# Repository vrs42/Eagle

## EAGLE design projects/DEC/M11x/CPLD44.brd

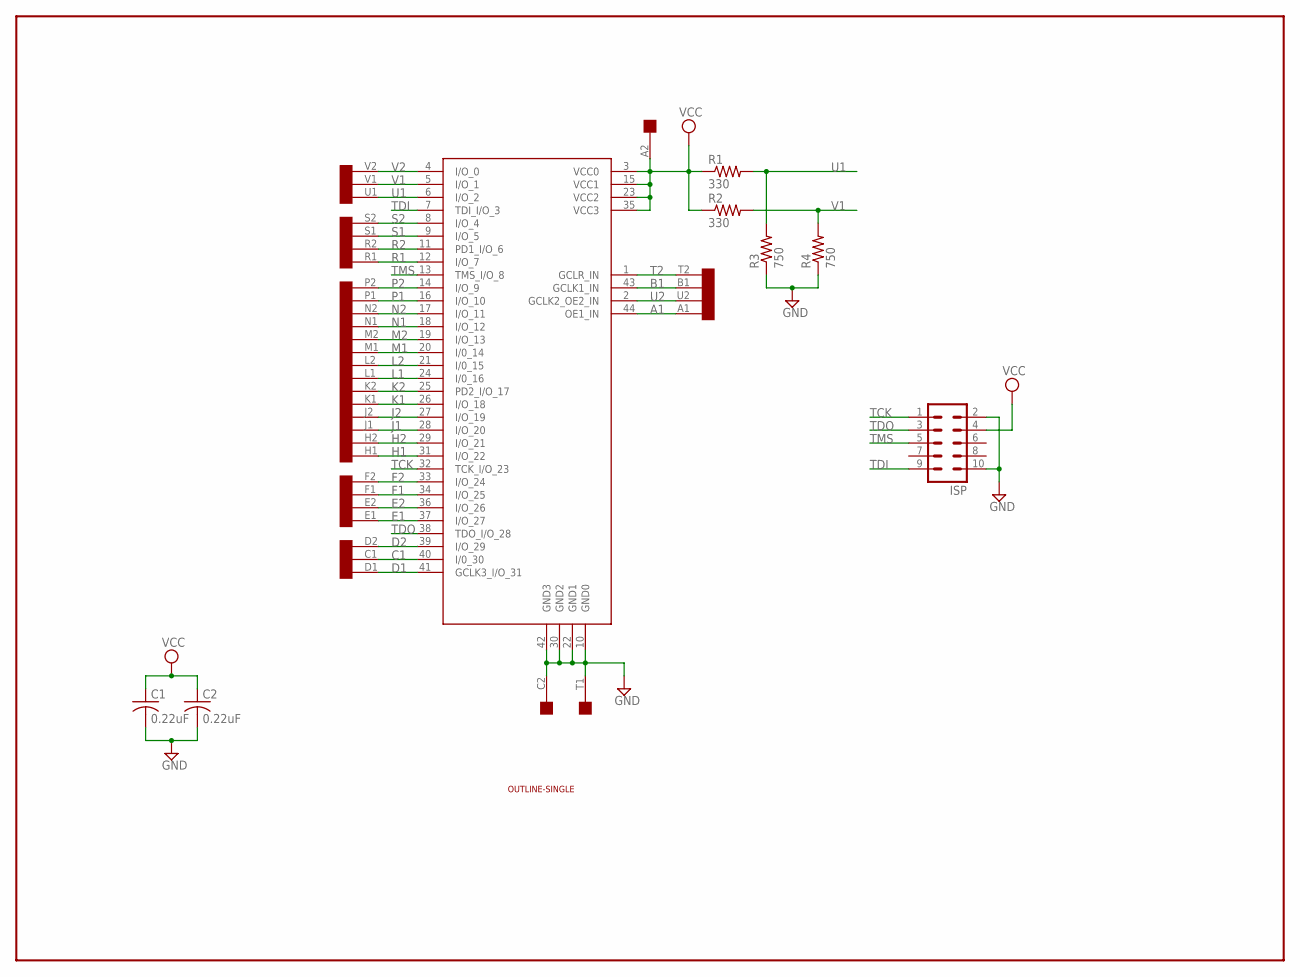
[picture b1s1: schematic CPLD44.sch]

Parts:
C1, C2: 0.22uF; C050-025X075
E1: ATF1502PLCC44; 3M44
ISP: MA05-2
R1, R2: 330; 0207/10
R3, R4: 750; 0207/10
U$1: SINGLE; EDGE-CON2
U$3: OUTLINE-SINGLE; SINGLE

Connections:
A1: E1.44 (OE1_IN), U$1.A1
B1: E1.43 (GCLK1_IN), U$1.B1
C1: E1.40 (I/0_30), U$1.C1
D1: E1.41 (GCLK3_I/O_31), U$1.D1
D2: E1.39 (I/O_29), U$1.D2
E1: E1.37 (I/O_27), U$1.E1
E2: E1.36 (I/O_26), U$1.E2
F1: E1.34 (I/O_25), U$1.F1
F2: E1.33 (I/O_24), U$1.F2
GND: C1.2, C2.2, E1.10 (GND0), E1.22 (GND1), E1.30 (GND2), E1.42 (GND3), ISP.2, ISP.10, R3.1, R4.1, U$1.C2, U$1.T1
H1: E1.31 (I/O_22), U$1.H1
H2: E1.29 (I/O_21), U$1.H2
J1: E1.28 (I/O_20), U$1.J1
J2: E1.27 (I/O_19), U$1.J2
K1: E1.26 (I/O_18), U$1.K1
K2: E1.25 (PD2_I/O_17), U$1.K2
L1: E1.24 (I/0_16), U$1.L1
L2: E1.21 (I/0_15), U$1.L2
M1: E1.20 (I/0_14), U$1.M1
M2: E1.19 (I/O_13), U$1.M2
N1: E1.18 (I/O_12), U$1.N1
N2: E1.17 (I/O_11), U$1.N2
P1: E1.16 (I/O_10), U$1.P1
P2: E1.14 (I/O_9), U$1.P2
R1: E1.12 (I/O_7), U$1.R1
R2: E1.11 (PD1_I/O_6), U$1.R2
S1: E1.9 (I/O_5), U$1.S1
S2: E1.8 (I/O_4), U$1.S2
T2: E1.1 (GCLR_IN), U$1.T2
TCK: E1.32 (TCK_I/O_23), ISP.1
TDI: E1.7 (TDI_I/O_3), ISP.9
TDO: E1.38 (TDO_I/O_28), ISP.3
TMS: E1.13 (TMS_I/O_8), ISP.5
U1: E1.6 (I/O_2), R1.2, R3.2, U$1.U1
U2: E1.2 (GCLK2_OE2_IN), U$1.U2
V1: E1.5 (I/O_1), R2.2, R4.2, U$1.V1
V2: E1.4 (I/O_0), U$1.V2
VCC: C1.1, C2.1, E1.3 (VCC0), E1.15 (VCC1), E1.23 (VCC2), E1.35 (VCC3), ISP.4, R1.1, R2.1, U$1.A2

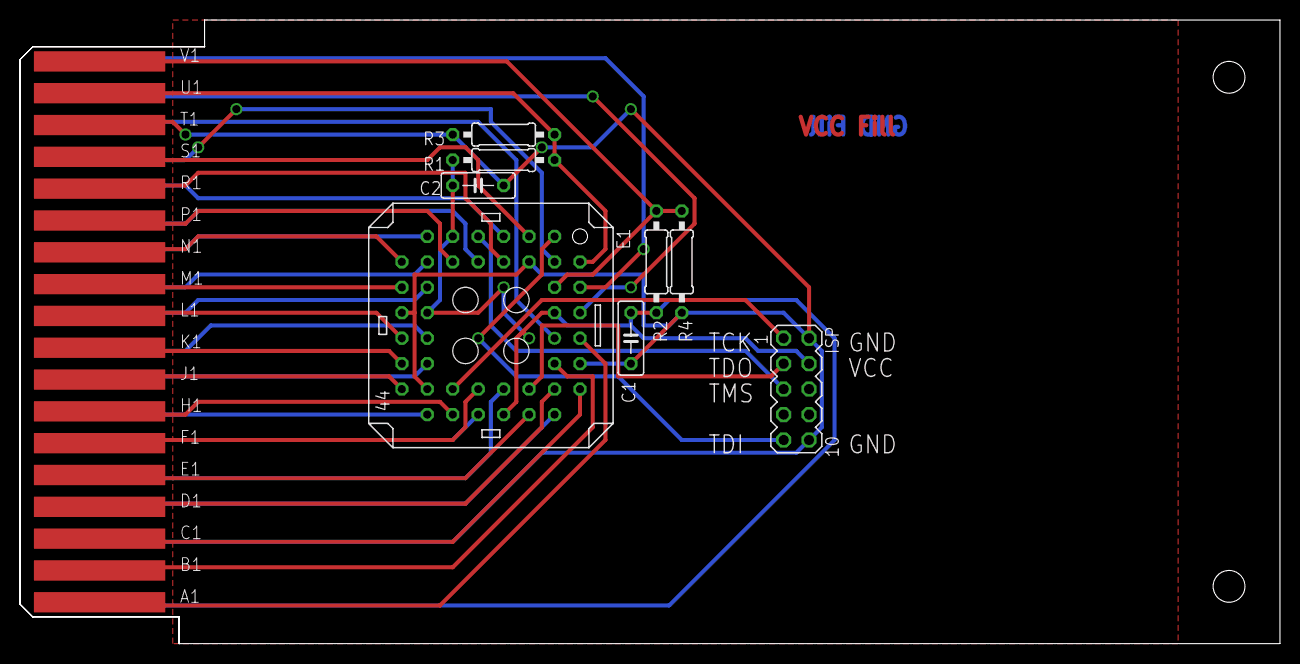
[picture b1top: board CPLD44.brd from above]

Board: 2 copper layers, 125.7 x 62.2 mm, 10 parts (0 on the bottom side), 38 nets.

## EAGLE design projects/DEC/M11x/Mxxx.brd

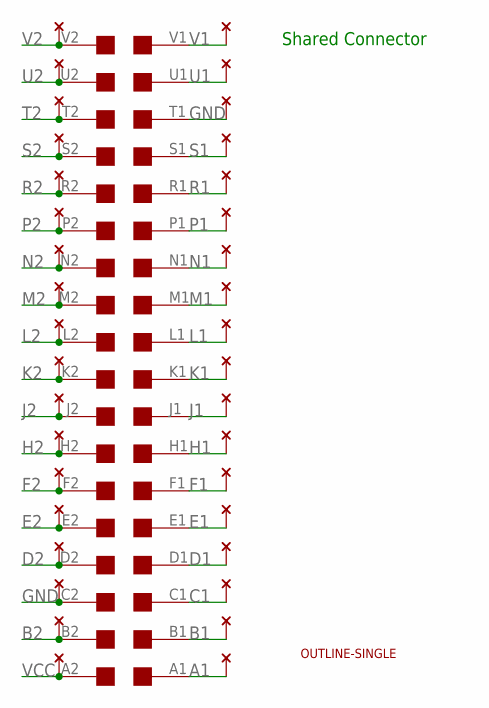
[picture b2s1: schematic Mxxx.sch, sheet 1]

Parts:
U$1: EDGE-2CONNECTOR; EDGE-CON2
U$4: THRU-HOLE2A; THRU-HOLEA
U$5: OUTLINE-SINGLE; SINGLE

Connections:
A1: U$1.A1, U$4.A1; also elsewhere on the board
B1: U$1.B1, U$4.B1; also elsewhere on the board
B2: U$1.B2, U$4.B2
C1: U$1.C1, U$4.C1; also elsewhere on the board
D1: U$1.D1, U$4.D1; also elsewhere on the board
D2: U$1.D2, U$4.D2; also elsewhere on the board
E1: U$1.E1, U$4.E1; also elsewhere on the board
E2: U$1.E2, U$4.E2; also elsewhere on the board
F1: U$1.F1, U$4.F1; also elsewhere on the board
F2: U$1.F2, U$4.F2; also elsewhere on the board
GND: U$1.C2, U$1.T1, U$4.C2, U$4.T1; also elsewhere on the board
H1: U$1.H1, U$4.H1; also elsewhere on the board
H2: U$1.H2, U$4.H2; also elsewhere on the board
J1: U$1.J1, U$4.J1; also elsewhere on the board
J2: U$1.J2, U$4.J2; also elsewhere on the board
K1: U$1.K1, U$4.K1; also elsewhere on the board
K2: U$1.K2, U$4.K2; also elsewhere on the board
L1: U$1.L1, U$4.L1; also elsewhere on the board
L2: U$1.L2, U$4.L2; also elsewhere on the board
M1: U$1.M1, U$4.M1; also elsewhere on the board
M2: U$1.M2, U$4.M2; also elsewhere on the board
N1: U$1.N1, U$4.N1; also elsewhere on the board
N2: U$1.N2, U$4.N2; also elsewhere on the board
P1: U$1.P1, U$4.P1; also elsewhere on the board
P2: U$1.P2, U$4.P2; also elsewhere on the board
R1: U$1.R1, U$4.R1; also elsewhere on the board
R2: U$1.R2, U$4.R2; also elsewhere on the board
S1: U$1.S1, U$4.S2; also elsewhere on the board
S2: U$1.S2, U$4.S1; also elsewhere on the board
T2: U$1.T2, U$4.T2; also elsewhere on the board
U1: U$1.U1, U$4.U1; also elsewhere on the board
U2: U$1.U2, U$4.U2; also elsewhere on the board
V1: U$1.V1, U$4.V1; also elsewhere on the board
V2: U$1.V2, U$4.V2; also elsewhere on the board
VCC: U$1.A2, U$4.A2; also elsewhere on the board

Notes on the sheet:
Shared Connector

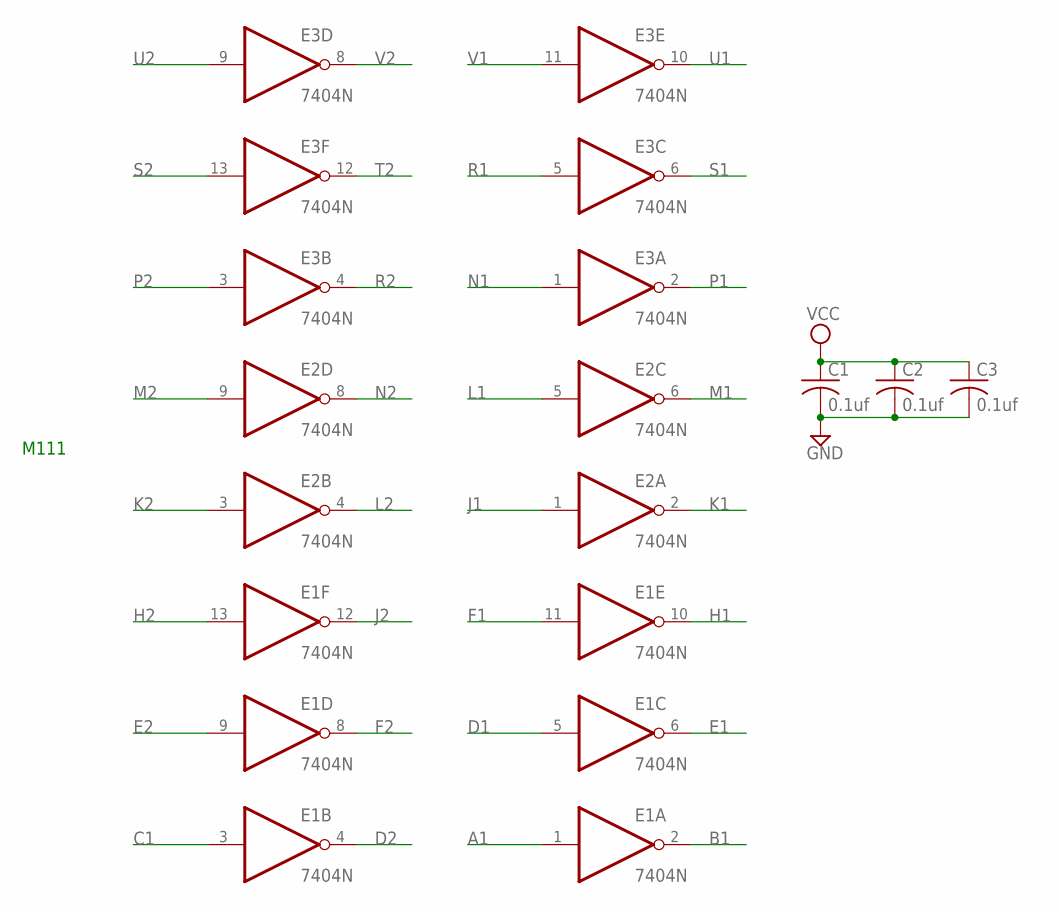
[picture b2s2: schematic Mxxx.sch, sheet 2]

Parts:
C1, C2, C3: 0.1uf; C050-025X075
E1, E2, E3: 7404N; DIL14

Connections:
A1: E1.1 (I); also elsewhere on the board
B1: E1.2 (O); also elsewhere on the board
C1: E1.3 (I); also elsewhere on the board
D1: E1.5 (I); also elsewhere on the board
D2: E1.4 (O); also elsewhere on the board
E1: E1.6 (O); also elsewhere on the board
E2: E1.9 (I); also elsewhere on the board
F1: E1.11 (I); also elsewhere on the board
F2: E1.8 (O); also elsewhere on the board
GND: C1.2, C2.2, C3.2, E1.7 (GND), E2.7 (GND), E3.7 (GND); also elsewhere on the board
H1: E1.10 (O); also elsewhere on the board
H2: E1.13 (I); also elsewhere on the board
J1: E2.1 (I); also elsewhere on the board
J2: E1.12 (O); also elsewhere on the board
K1: E2.2 (O); also elsewhere on the board
K2: E2.3 (I); also elsewhere on the board
L1: E2.5 (I); also elsewhere on the board
L2: E2.4 (O); also elsewhere on the board
M1: E2.6 (O); also elsewhere on the board
M2: E2.9 (I); also elsewhere on the board
N1: E3.1 (I); also elsewhere on the board
N2: E2.8 (O); also elsewhere on the board
P1: E3.2 (O); also elsewhere on the board
P2: E3.3 (I); also elsewhere on the board
R1: E3.5 (I); also elsewhere on the board
R2: E3.4 (O); also elsewhere on the board
S1: E3.6 (O); also elsewhere on the board
S2: E3.13 (I); also elsewhere on the board
T2: E3.12 (O); also elsewhere on the board
U1: E3.10 (O); also elsewhere on the board
U2: E3.9 (I); also elsewhere on the board
V1: E3.11 (I); also elsewhere on the board
V2: E3.8 (O); also elsewhere on the board
VCC: C1.1, C2.1, C3.1, E1.14 (VCC), E2.14 (VCC), E3.14 (VCC); also elsewhere on the board

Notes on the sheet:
M111

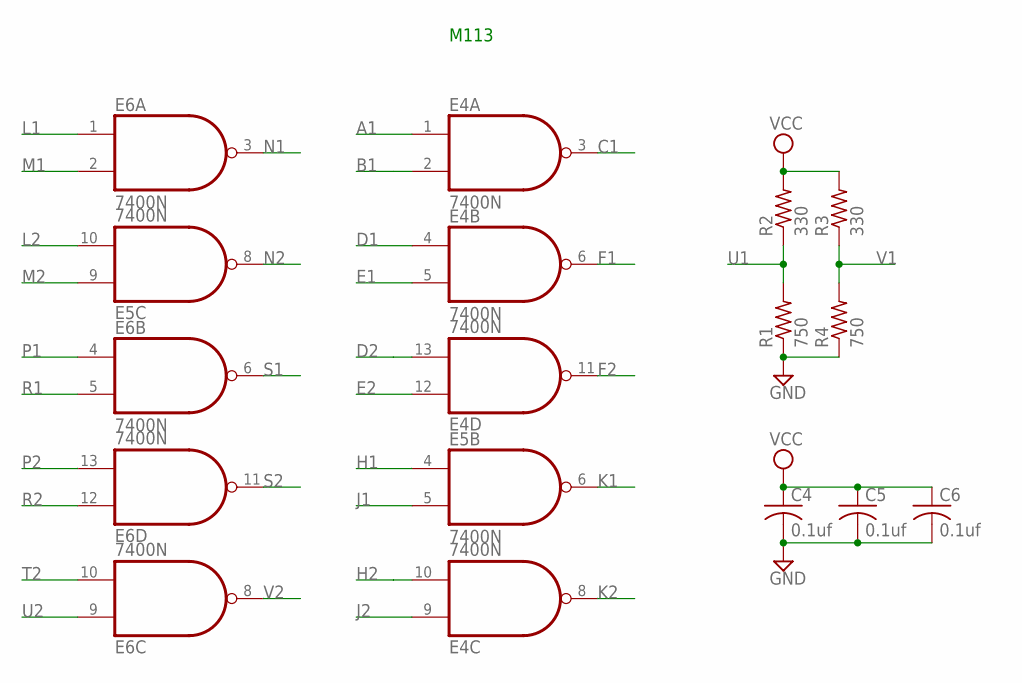
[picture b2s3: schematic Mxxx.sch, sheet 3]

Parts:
C4, C5, C6: 0.1uf; C050-025X075
E4, E5, E6: 7400N; DIL14
R1, R4: 750; 0207/10
R2, R3: 330; 0207/10

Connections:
A1: E4.1 (I0); also elsewhere on the board
B1: E4.2 (I1); also elsewhere on the board
C1: E4.3 (O); also elsewhere on the board
D1: E4.4 (I0); also elsewhere on the board
D2: E4.13 (I1); also elsewhere on the board
E1: E4.5 (I1); also elsewhere on the board
E2: E4.12 (I0); also elsewhere on the board
F1: E4.6 (O); also elsewhere on the board
F2: E4.11 (O); also elsewhere on the board
GND: C4.2, C5.2, C6.2, E4.7 (GND), E5.7 (GND), E6.7 (GND), R1.1, R4.1; also elsewhere on the board
H1: E5.4 (I0); also elsewhere on the board
H2: E4.10 (I1); also elsewhere on the board
J1: E5.5 (I1); also elsewhere on the board
J2: E4.9 (I0); also elsewhere on the board
K1: E5.6 (O); also elsewhere on the board
K2: E4.8 (O); also elsewhere on the board
L1: E6.1 (I0); also elsewhere on the board
L2: E5.10 (I1); also elsewhere on the board
M1: E6.2 (I1); also elsewhere on the board
M2: E5.9 (I0); also elsewhere on the board
N1: E6.3 (O); also elsewhere on the board
N2: E5.8 (O); also elsewhere on the board
P1: E6.4 (I0); also elsewhere on the board
P2: E6.13 (I1); also elsewhere on the board
R1: E6.5 (I1); also elsewhere on the board
R2: E6.12 (I0); also elsewhere on the board
S1: E6.6 (O); also elsewhere on the board
S2: E6.11 (O); also elsewhere on the board
T2: E6.10 (I1); also elsewhere on the board
U1: R1.2, R2.1; also elsewhere on the board
U2: E6.9 (I0); also elsewhere on the board
V1: R3.1, R4.2; also elsewhere on the board
V2: E6.8 (O); also elsewhere on the board
VCC: C4.1, C5.1, C6.1, E4.14 (VCC), E5.14 (VCC), E6.14 (VCC), R2.2, R3.2; also elsewhere on the board

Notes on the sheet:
M113

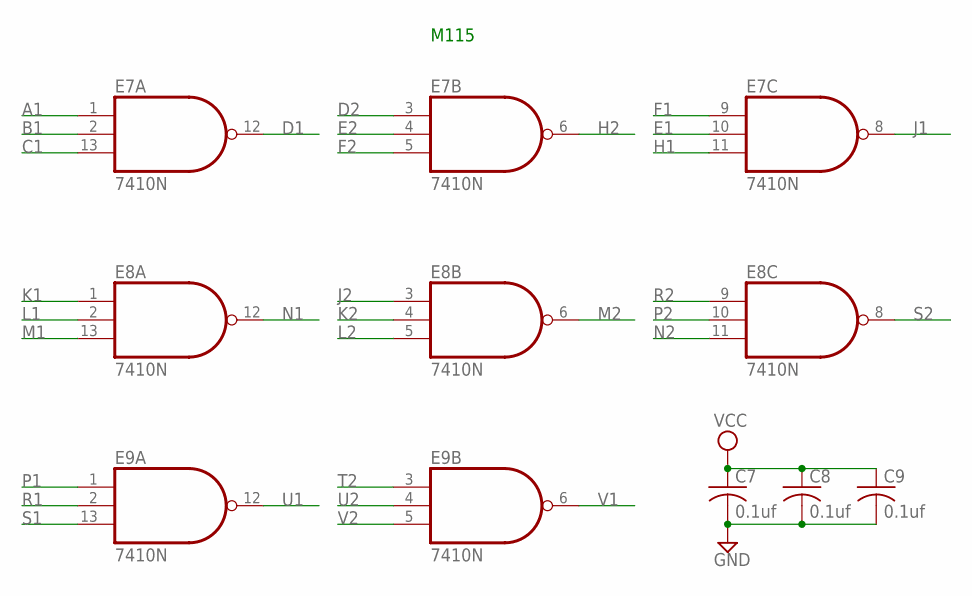
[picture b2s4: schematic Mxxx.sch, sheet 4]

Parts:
C7, C8, C9: 0.1uf; C050-025X075
E7, E8, E9: 7410N; DIL14

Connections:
A1: E7.1 (I0); also elsewhere on the board
B1: E7.2 (I1); also elsewhere on the board
C1: E7.13 (I2); also elsewhere on the board
D1: E7.12 (O); also elsewhere on the board
D2: E7.3 (I0); also elsewhere on the board
E1: E7.10 (I1); also elsewhere on the board
E2: E7.4 (I1); also elsewhere on the board
F1: E7.9 (I0); also elsewhere on the board
F2: E7.5 (I2); also elsewhere on the board
GND: C7.2, C8.2, C9.2, E7.7 (GND), E8.7 (GND), E9.7 (GND); also elsewhere on the board
H1: E7.11 (I2); also elsewhere on the board
H2: E7.6 (O); also elsewhere on the board
J1: E7.8 (O); also elsewhere on the board
J2: E8.3 (I0); also elsewhere on the board
K1: E8.1 (I0); also elsewhere on the board
K2: E8.4 (I1); also elsewhere on the board
L1: E8.2 (I1); also elsewhere on the board
L2: E8.5 (I2); also elsewhere on the board
M1: E8.13 (I2); also elsewhere on the board
M2: E8.6 (O); also elsewhere on the board
N1: E8.12 (O); also elsewhere on the board
N2: E8.11 (I2); also elsewhere on the board
P1: E9.1 (I0); also elsewhere on the board
P2: E8.10 (I1); also elsewhere on the board
R1: E9.2 (I1); also elsewhere on the board
R2: E8.9 (I0); also elsewhere on the board
S1: E9.13 (I2); also elsewhere on the board
S2: E8.8 (O); also elsewhere on the board
T2: E9.3 (I0); also elsewhere on the board
U1: E9.12 (O); also elsewhere on the board
U2: E9.4 (I1); also elsewhere on the board
V1: E9.6 (O); also elsewhere on the board
V2: E9.5 (I2); also elsewhere on the board
VCC: C7.1, C8.1, C9.1, E7.14 (VCC), E8.14 (VCC), E9.14 (VCC); also elsewhere on the board

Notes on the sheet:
M115

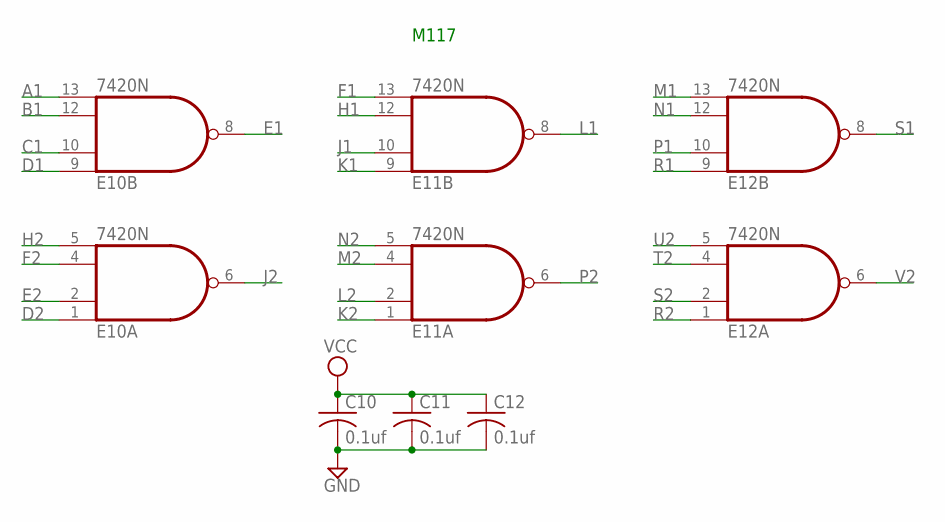
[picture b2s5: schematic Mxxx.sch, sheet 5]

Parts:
C10, C11, C12: 0.1uf; C050-025X075
E10, E11, E12: 7420N; DIL14

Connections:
A1: E10.13 (I3); also elsewhere on the board
B1: E10.12 (I2); also elsewhere on the board
C1: E10.10 (I1); also elsewhere on the board
D1: E10.9 (I0); also elsewhere on the board
D2: E10.1 (I0); also elsewhere on the board
E1: E10.8 (O); also elsewhere on the board
E2: E10.2 (I1); also elsewhere on the board
F1: E11.13 (I3); also elsewhere on the board
F2: E10.4 (I2); also elsewhere on the board
GND: C10.2, C11.2, C12.2, E10.7 (GND), E11.7 (GND), E12.7 (GND); also elsewhere on the board
H1: E11.12 (I2); also elsewhere on the board
H2: E10.5 (I3); also elsewhere on the board
J1: E11.10 (I1); also elsewhere on the board
J2: E10.6 (O); also elsewhere on the board
K1: E11.9 (I0); also elsewhere on the board
K2: E11.1 (I0); also elsewhere on the board
L1: E11.8 (O); also elsewhere on the board
L2: E11.2 (I1); also elsewhere on the board
M1: E12.13 (I3); also elsewhere on the board
M2: E11.4 (I2); also elsewhere on the board
N1: E12.12 (I2); also elsewhere on the board
N2: E11.5 (I3); also elsewhere on the board
P1: E12.10 (I1); also elsewhere on the board
P2: E11.6 (O); also elsewhere on the board
R1: E12.9 (I0); also elsewhere on the board
R2: E12.1 (I0); also elsewhere on the board
S1: E12.8 (O); also elsewhere on the board
S2: E12.2 (I1); also elsewhere on the board
T2: E12.4 (I2); also elsewhere on the board
U2: E12.5 (I3); also elsewhere on the board
V2: E12.6 (O); also elsewhere on the board
VCC: C10.1, C11.1, C12.1, E10.14 (VCC), E11.14 (VCC), E12.14 (VCC); also elsewhere on the board

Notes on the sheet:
M117

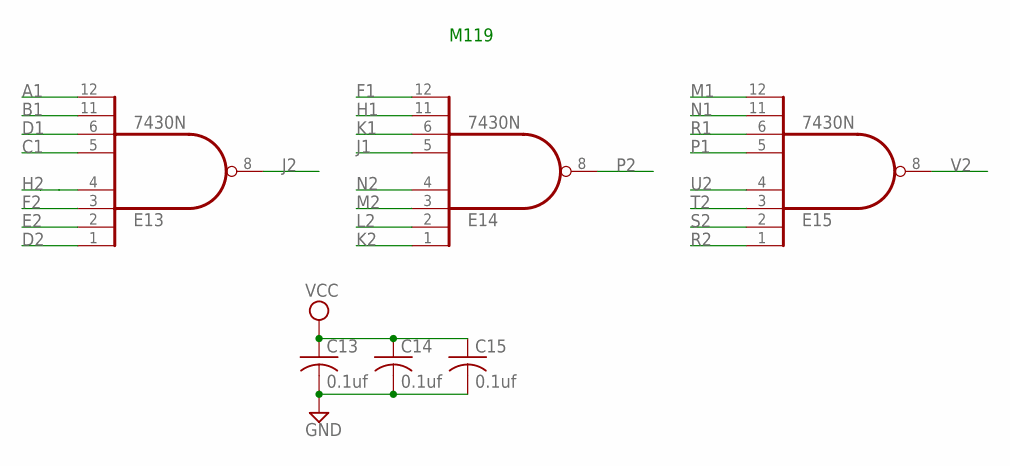
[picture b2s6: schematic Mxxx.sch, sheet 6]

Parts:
C13, C14, C15: 0.1uf; C050-025X075
E13, E14, E15: 7430N; DIL14

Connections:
A1: E13.12 (I7); also elsewhere on the board
B1: E13.11 (I6); also elsewhere on the board
C1: E13.5 (I4); also elsewhere on the board
D1: E13.6 (I5); also elsewhere on the board
D2: E13.1 (I0); also elsewhere on the board
E2: E13.2 (I1); also elsewhere on the board
F1: E14.12 (I7); also elsewhere on the board
F2: E13.3 (I2); also elsewhere on the board
GND: C13.2, C14.2, C15.2, E13.7 (GND), E14.7 (GND), E15.7 (GND); also elsewhere on the board
H1: E14.11 (I6); also elsewhere on the board
H2: E13.4 (I3); also elsewhere on the board
J1: E14.5 (I4); also elsewhere on the board
J2: E13.8 (O); also elsewhere on the board
K1: E14.6 (I5); also elsewhere on the board
K2: E14.1 (I0); also elsewhere on the board
L2: E14.2 (I1); also elsewhere on the board
M1: E15.12 (I7); also elsewhere on the board
M2: E14.3 (I2); also elsewhere on the board
N1: E15.11 (I6); also elsewhere on the board
N2: E14.4 (I3); also elsewhere on the board
P1: E15.5 (I4); also elsewhere on the board
P2: E14.8 (O); also elsewhere on the board
R1: E15.6 (I5); also elsewhere on the board
R2: E15.1 (I0); also elsewhere on the board
S2: E15.2 (I1); also elsewhere on the board
T2: E15.3 (I2); also elsewhere on the board
U2: E15.4 (I3); also elsewhere on the board
V2: E15.8 (O); also elsewhere on the board
VCC: C13.1, C14.1, C15.1, E13.14 (VCC), E14.14 (VCC), E15.14 (VCC); also elsewhere on the board

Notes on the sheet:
M119

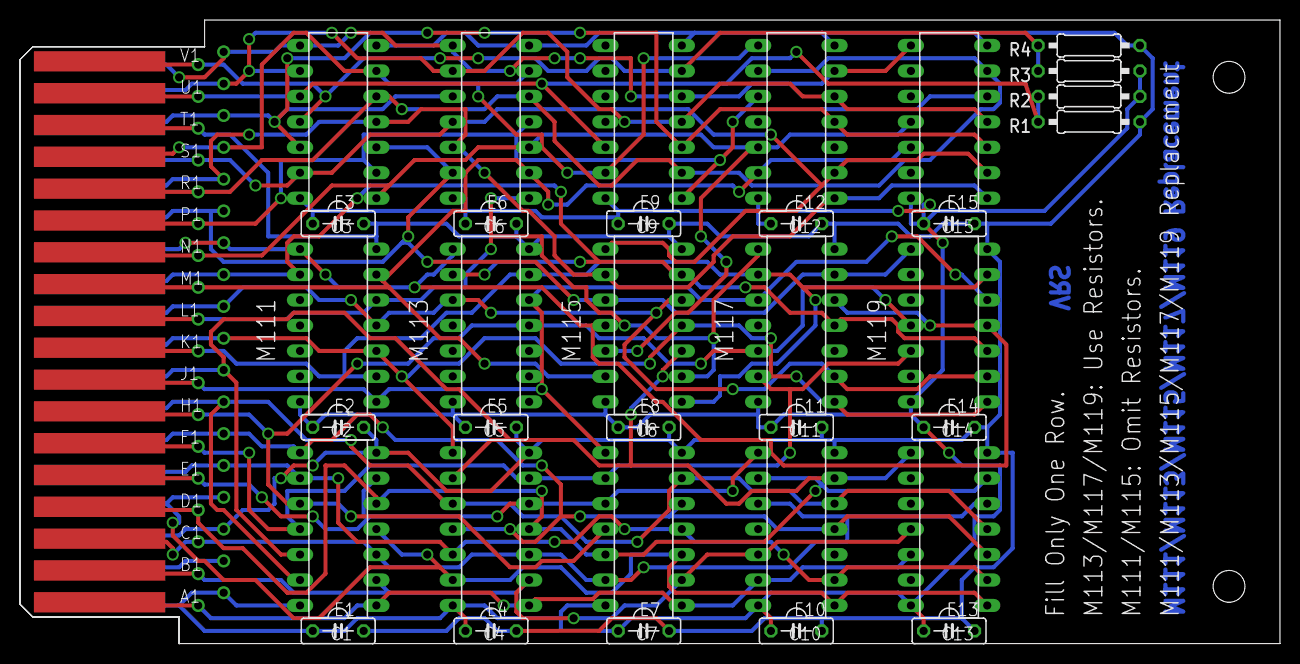
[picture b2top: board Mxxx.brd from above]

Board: 2 copper layers, 125.7 x 62.2 mm, 37 parts (0 on the bottom side), 35 nets.

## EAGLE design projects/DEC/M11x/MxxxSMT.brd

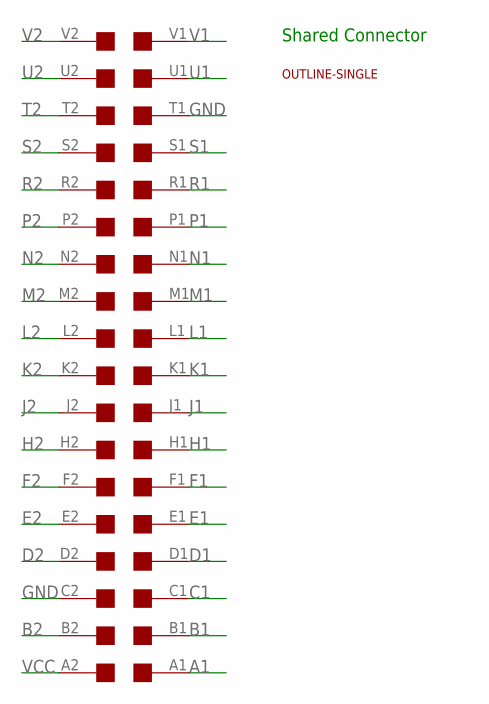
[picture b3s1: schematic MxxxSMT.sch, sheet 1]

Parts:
U$1: EDGE-2CONNECTOR; EDGE-CON2
U$4: OUTLINE-SINGLE; SINGLE

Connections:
A1: U$1.A1; also elsewhere on the board
B1: U$1.B1; also elsewhere on the board
B2: U$1.B2
C1: U$1.C1; also elsewhere on the board
D1: U$1.D1; also elsewhere on the board
D2: U$1.D2; also elsewhere on the board
E1: U$1.E1; also elsewhere on the board
E2: U$1.E2; also elsewhere on the board
F1: U$1.F1; also elsewhere on the board
F2: U$1.F2; also elsewhere on the board
GND: U$1.C2, U$1.T1; also elsewhere on the board
H1: U$1.H1; also elsewhere on the board
H2: U$1.H2; also elsewhere on the board
J1: U$1.J1; also elsewhere on the board
J2: U$1.J2; also elsewhere on the board
K1: U$1.K1; also elsewhere on the board
K2: U$1.K2; also elsewhere on the board
L1: U$1.L1; also elsewhere on the board
L2: U$1.L2; also elsewhere on the board
M1: U$1.M1; also elsewhere on the board
M2: U$1.M2; also elsewhere on the board
N1: U$1.N1; also elsewhere on the board
N2: U$1.N2; also elsewhere on the board
P1: U$1.P1; also elsewhere on the board
P2: U$1.P2; also elsewhere on the board
R1: U$1.R1; also elsewhere on the board
R2: U$1.R2; also elsewhere on the board
S1: U$1.S1; also elsewhere on the board
S2: U$1.S2; also elsewhere on the board
T2: U$1.T2; also elsewhere on the board
U1: U$1.U1; also elsewhere on the board
U2: U$1.U2; also elsewhere on the board
V1: U$1.V1; also elsewhere on the board
V2: U$1.V2; also elsewhere on the board
VCC: U$1.A2; also elsewhere on the board

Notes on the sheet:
Shared Connector

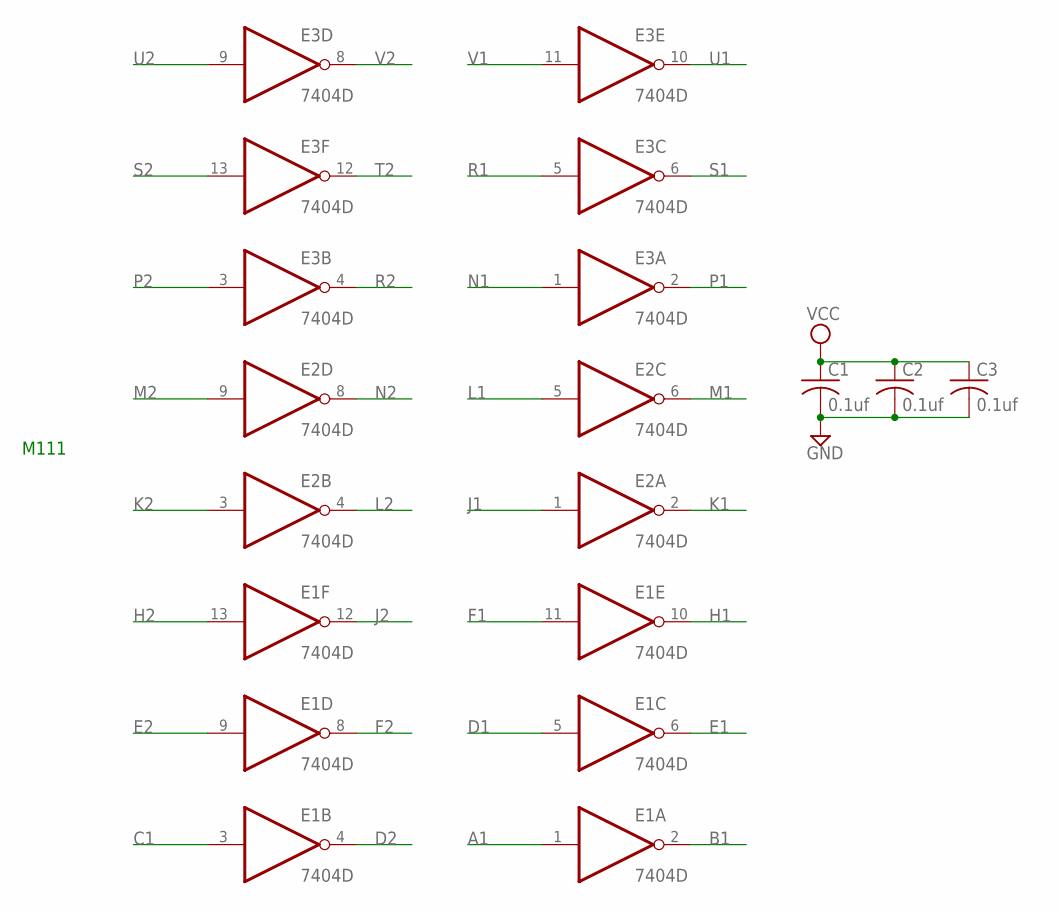
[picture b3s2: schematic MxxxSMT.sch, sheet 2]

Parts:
C1, C2, C3: 0.1uf; C050-025X075
E1, E2, E3: 7404D; SO14

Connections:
A1: E1.1 (I); also elsewhere on the board
B1: E1.2 (O); also elsewhere on the board
C1: E1.3 (I); also elsewhere on the board
D1: E1.5 (I); also elsewhere on the board
D2: E1.4 (O); also elsewhere on the board
E1: E1.6 (O); also elsewhere on the board
E2: E1.9 (I); also elsewhere on the board
F1: E1.11 (I); also elsewhere on the board
F2: E1.8 (O); also elsewhere on the board
GND: C1.2, C2.2, C3.2, E1.7 (GND), E2.7 (GND), E3.7 (GND); also elsewhere on the board
H1: E1.10 (O); also elsewhere on the board
H2: E1.13 (I); also elsewhere on the board
J1: E2.1 (I); also elsewhere on the board
J2: E1.12 (O); also elsewhere on the board
K1: E2.2 (O); also elsewhere on the board
K2: E2.3 (I); also elsewhere on the board
L1: E2.5 (I); also elsewhere on the board
L2: E2.4 (O); also elsewhere on the board
M1: E2.6 (O); also elsewhere on the board
M2: E2.9 (I); also elsewhere on the board
N1: E3.1 (I); also elsewhere on the board
N2: E2.8 (O); also elsewhere on the board
P1: E3.2 (O); also elsewhere on the board
P2: E3.3 (I); also elsewhere on the board
R1: E3.5 (I); also elsewhere on the board
R2: E3.4 (O); also elsewhere on the board
S1: E3.6 (O); also elsewhere on the board
S2: E3.13 (I); also elsewhere on the board
T2: E3.12 (O); also elsewhere on the board
U1: E3.10 (O); also elsewhere on the board
U2: E3.9 (I); also elsewhere on the board
V1: E3.11 (I); also elsewhere on the board
V2: E3.8 (O); also elsewhere on the board
VCC: C1.1, C2.1, C3.1, E1.14 (VCC), E2.14 (VCC), E3.14 (VCC); also elsewhere on the board

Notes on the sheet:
M111

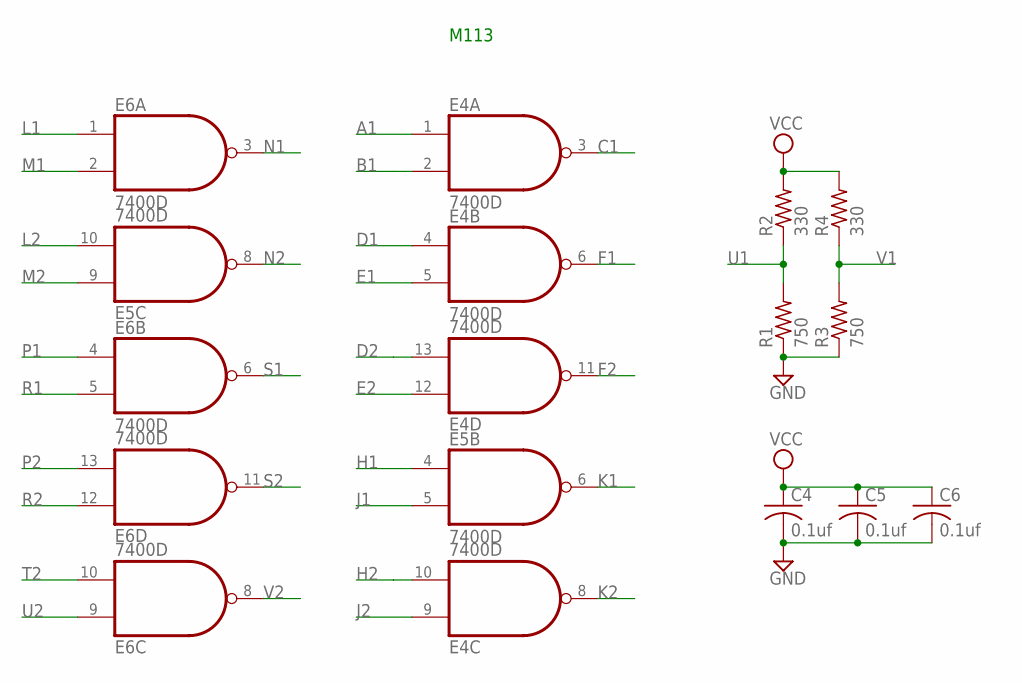
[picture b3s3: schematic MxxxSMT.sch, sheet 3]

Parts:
C4, C5, C6: 0.1uf; C050-025X075
E4, E5, E6: 7400D; SO14
R1, R3: 750; 0207/10
R2, R4: 330; 0207/10

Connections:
A1: E4.1 (I0); also elsewhere on the board
B1: E4.2 (I1); also elsewhere on the board
C1: E4.3 (O); also elsewhere on the board
D1: E4.4 (I0); also elsewhere on the board
D2: E4.13 (I1); also elsewhere on the board
E1: E4.5 (I1); also elsewhere on the board
E2: E4.12 (I0); also elsewhere on the board
F1: E4.6 (O); also elsewhere on the board
F2: E4.11 (O); also elsewhere on the board
GND: C4.2, C5.2, C6.2, E4.7 (GND), E5.7 (GND), E6.7 (GND), R1.1, R3.1; also elsewhere on the board
H1: E5.4 (I0); also elsewhere on the board
H2: E4.10 (I1); also elsewhere on the board
J1: E5.5 (I1); also elsewhere on the board
J2: E4.9 (I0); also elsewhere on the board
K1: E5.6 (O); also elsewhere on the board
K2: E4.8 (O); also elsewhere on the board
L1: E6.1 (I0); also elsewhere on the board
L2: E5.10 (I1); also elsewhere on the board
M1: E6.2 (I1); also elsewhere on the board
M2: E5.9 (I0); also elsewhere on the board
N1: E6.3 (O); also elsewhere on the board
N2: E5.8 (O); also elsewhere on the board
P1: E6.4 (I0); also elsewhere on the board
P2: E6.13 (I1); also elsewhere on the board
R1: E6.5 (I1); also elsewhere on the board
R2: E6.12 (I0); also elsewhere on the board
S1: E6.6 (O); also elsewhere on the board
S2: E6.11 (O); also elsewhere on the board
T2: E6.10 (I1); also elsewhere on the board
U1: R1.2, R2.1; also elsewhere on the board
U2: E6.9 (I0); also elsewhere on the board
V1: R3.2, R4.1; also elsewhere on the board
V2: E6.8 (O); also elsewhere on the board
VCC: C4.1, C5.1, C6.1, E4.14 (VCC), E5.14 (VCC), E6.14 (VCC), R2.2, R4.2; also elsewhere on the board

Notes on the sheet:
M113

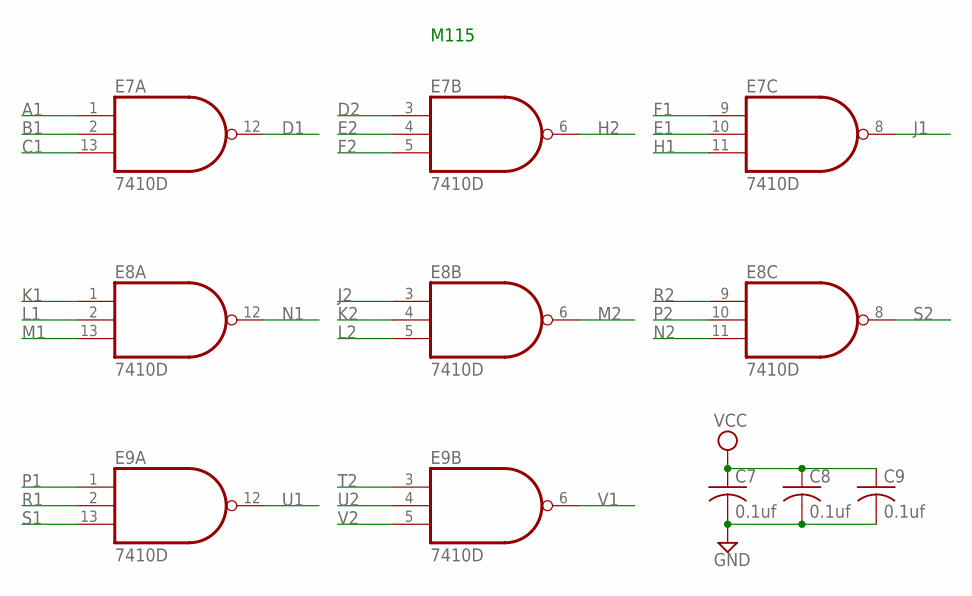
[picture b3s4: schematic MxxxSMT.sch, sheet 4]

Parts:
C7, C8, C9: 0.1uf; C050-025X075
E7, E8, E9: 7410D; SO14

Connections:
A1: E7.1 (I0); also elsewhere on the board
B1: E7.2 (I1); also elsewhere on the board
C1: E7.13 (I2); also elsewhere on the board
D1: E7.12 (O); also elsewhere on the board
D2: E7.3 (I0); also elsewhere on the board
E1: E7.10 (I1); also elsewhere on the board
E2: E7.4 (I1); also elsewhere on the board
F1: E7.9 (I0); also elsewhere on the board
F2: E7.5 (I2); also elsewhere on the board
GND: C7.2, C8.2, C9.2, E7.7 (GND), E8.7 (GND), E9.7 (GND); also elsewhere on the board
H1: E7.11 (I2); also elsewhere on the board
H2: E7.6 (O); also elsewhere on the board
J1: E7.8 (O); also elsewhere on the board
J2: E8.3 (I0); also elsewhere on the board
K1: E8.1 (I0); also elsewhere on the board
K2: E8.4 (I1); also elsewhere on the board
L1: E8.2 (I1); also elsewhere on the board
L2: E8.5 (I2); also elsewhere on the board
M1: E8.13 (I2); also elsewhere on the board
M2: E8.6 (O); also elsewhere on the board
N1: E8.12 (O); also elsewhere on the board
N2: E8.11 (I2); also elsewhere on the board
P1: E9.1 (I0); also elsewhere on the board
P2: E8.10 (I1); also elsewhere on the board
R1: E9.2 (I1); also elsewhere on the board
R2: E8.9 (I0); also elsewhere on the board
S1: E9.13 (I2); also elsewhere on the board
S2: E8.8 (O); also elsewhere on the board
T2: E9.3 (I0); also elsewhere on the board
U1: E9.12 (O); also elsewhere on the board
U2: E9.4 (I1); also elsewhere on the board
V1: E9.6 (O); also elsewhere on the board
V2: E9.5 (I2); also elsewhere on the board
VCC: C7.1, C8.1, C9.1, E7.14 (VCC), E8.14 (VCC), E9.14 (VCC); also elsewhere on the board

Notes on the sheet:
M115

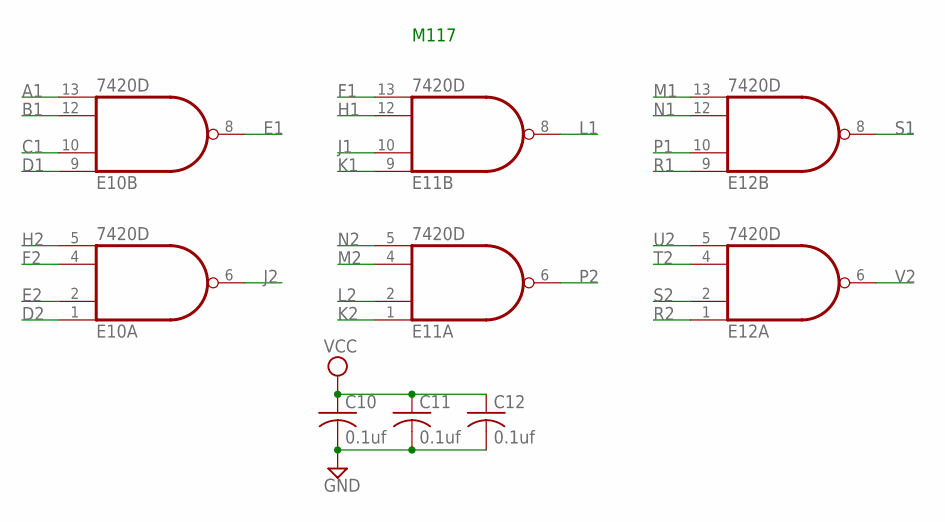
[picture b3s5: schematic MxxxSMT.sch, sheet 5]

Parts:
C10, C11, C12: 0.1uf; C050-025X075
E10, E11, E12: 7420D; SO14

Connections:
A1: E10.13 (I3); also elsewhere on the board
B1: E10.12 (I2); also elsewhere on the board
C1: E10.10 (I1); also elsewhere on the board
D1: E10.9 (I0); also elsewhere on the board
D2: E10.1 (I0); also elsewhere on the board
E1: E10.8 (O); also elsewhere on the board
E2: E10.2 (I1); also elsewhere on the board
F1: E11.13 (I3); also elsewhere on the board
F2: E10.4 (I2); also elsewhere on the board
GND: C10.2, C11.2, C12.2, E10.7 (GND), E11.7 (GND), E12.7 (GND); also elsewhere on the board
H1: E11.12 (I2); also elsewhere on the board
H2: E10.5 (I3); also elsewhere on the board
J1: E11.10 (I1); also elsewhere on the board
J2: E10.6 (O); also elsewhere on the board
K1: E11.9 (I0); also elsewhere on the board
K2: E11.1 (I0); also elsewhere on the board
L1: E11.8 (O); also elsewhere on the board
L2: E11.2 (I1); also elsewhere on the board
M1: E12.13 (I3); also elsewhere on the board
M2: E11.4 (I2); also elsewhere on the board
N1: E12.12 (I2); also elsewhere on the board
N2: E11.5 (I3); also elsewhere on the board
P1: E12.10 (I1); also elsewhere on the board
P2: E11.6 (O); also elsewhere on the board
R1: E12.9 (I0); also elsewhere on the board
R2: E12.1 (I0); also elsewhere on the board
S1: E12.8 (O); also elsewhere on the board
S2: E12.2 (I1); also elsewhere on the board
T2: E12.4 (I2); also elsewhere on the board
U2: E12.5 (I3); also elsewhere on the board
V2: E12.6 (O); also elsewhere on the board
VCC: C10.1, C11.1, C12.1, E10.14 (VCC), E11.14 (VCC), E12.14 (VCC); also elsewhere on the board

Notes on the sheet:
M117
